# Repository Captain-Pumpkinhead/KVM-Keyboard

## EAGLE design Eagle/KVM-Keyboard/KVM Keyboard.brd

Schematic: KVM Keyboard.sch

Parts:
A: KEYSWITCH-PLAIN-CHOC-1U; CHOC-1U
B: KEYSWITCH-PLAIN-CHOC-1U; CHOC-1U
BACKSLASH: KEYSWITCH-PLAIN-CHOC-1U; CHOC-1U
BACKSPACE: KEYSWITCH-PLAIN-CHOC-2U; CHOC-2U
BLUE_ROTENC: ENCODER-SWITCH; ROTARY_ENC_PLAIN
BRACE-CLOSING: KEYSWITCH-PLAIN-CHOC-1U; CHOC-1U
BRACE-OPENING: KEYSWITCH-PLAIN-CHOC-1U; CHOC-1U
BRIGHTNESS: ENCODER-SWITCH; ROTARY_ENC_PLAIN
BRIGHTNESS-MINUS: KEYSWITCH-PLAIN-CHOC-1U; CHOC-1U
BRIGHTNESS-PLUS: KEYSWITCH-PLAIN-CHOC-1U; CHOC-1U
C: KEYSWITCH-PLAIN-CHOC-1U; CHOC-1U
CALC: KEYSWITCH-PLAIN-CHOC-1U; CHOC-1U
CAPS-LOCK: KEYSWITCH-PLAIN-CHOC-1U; CHOC-1U
COLON: KEYSWITCH-PLAIN-CHOC-1U; CHOC-1U
D: KEYSWITCH-PLAIN-CHOC-1U; CHOC-1U
D1, D2, D3, D4, D5, D6, D7, D8, D9, D10, D11, D12: DIODESMALL; DIODE_SMALL
DELETE: KEYSWITCH-PLAIN-CHOC-1U; CHOC-1U
DOWN: KEYSWITCH-PLAIN-CHOC-1U; CHOC-1U
E: KEYSWITCH-PLAIN-CHOC-1U; CHOC-1U
END: KEYSWITCH-PLAIN-CHOC-1U; CHOC-1U
ENTER: KEYSWITCH-PLAIN-CHOC-2U; CHOC-2U
ESC: KEYSWITCH-PLAIN-CHOC-1U; CHOC-1U
F, F1, F2, F3, F4, F5, F6, F7, F8, F9, F10, F11, F12: KEYSWITCH-PLAIN-CHOC-1U; CHOC-1U
FN: SWITCH_PUSHBUTTONEVQ-PE; TACT_PANA-EVQ
FOLDER: KEYSWITCH-PLAIN-CHOC-1U; CHOC-1U
G: KEYSWITCH-PLAIN-CHOC-1U; CHOC-1U
GREATER-THAN: KEYSWITCH-PLAIN-CHOC-1U; CHOC-1U
GREEN_ROTENC: ENCODER-SWITCH; ROTARY_ENC_PLAIN
H: KEYSWITCH-PLAIN-CHOC-1U; CHOC-1U
HIBERNATE: KEYSWITCH-PLAIN-CHOC-1U; CHOC-1U
HOME: KEYSWITCH-PLAIN-CHOC-1U; CHOC-1U
I: KEYSWITCH-PLAIN-CHOC-1U; CHOC-1U
INSERT: KEYSWITCH-PLAIN-CHOC-1U; CHOC-1U
J: KEYSWITCH-PLAIN-CHOC-1U; CHOC-1U
K: KEYSWITCH-PLAIN-CHOC-1U; CHOC-1U
KVM_PC1, KVM_PC2, KVM_PC3, KVM_PC4: KEYSWITCH-PLAIN-CHOC-1U; CHOC-1U
L: KEYSWITCH-PLAIN-CHOC-1U; CHOC-1U
LCD-BUTTON-BOTTOM: SWITCH_PUSHBUTTONEVQ-PE; TACT_PANA-EVQ
LCD-BUTTON-TOP: SWITCH_PUSHBUTTONEVQ-PE; TACT_PANA-EVQ
LEFT: KEYSWITCH-PLAIN-CHOC-1U; CHOC-1U
LEFT-ALT: KEYSWITCH-PLAIN-CHOC-1U; CHOC-1U
LEFT-CTRL: KEYSWITCH-PLAIN-CHOC-1U; CHOC-1U
LEFT-SUPER: KEYSWITCH-PLAIN-CHOC-1U; CHOC-1U
LESS-THAN: KEYSWITCH-PLAIN-CHOC-1U; CHOC-1U
LSHIFT: KEYSWITCH-PLAIN-CHOC-2U; CHOC-2U
M: KEYSWITCH-PLAIN-CHOC-1U; CHOC-1U
MENU: KEYSWITCH-PLAIN-CHOC-1U; CHOC-1U
MUTE: KEYSWITCH-PLAIN-CHOC-1U; CHOC-1U
N: KEYSWITCH-PLAIN-CHOC-1U; CHOC-1U
NEXT: KEYSWITCH-PLAIN-CHOC-1U; CHOC-1U
NOTES: KEYSWITCH-PLAIN-CHOC-1U; CHOC-1U
NUM0, NUM1, NUM2, NUM3, NUM4, NUM5, NUM6, NUM7, NUM8, NUM9: KEYSWITCH-PLAIN-CHOC-1U; CHOC-1U
NUM-LOCK: KEYSWITCH-PLAIN-CHOC-1U; CHOC-1U
NUM-MINUS: KEYSWITCH-PLAIN-CHOC-1U; CHOC-1U
NUM-PLUS: KEYSWITCH-PLAIN-CHOC-1U; CHOC-1U
O: KEYSWITCH-PLAIN-CHOC-1U; CHOC-1U
P: KEYSWITCH-PLAIN-CHOC-1U; CHOC-1U
PAD0: KEYSWITCH-PLAIN-CHOC-2U; CHOC-2U
PAD1, PAD2, PAD3, PAD4, PAD5, PAD6, PAD7, PAD8, PAD9: KEYSWITCH-PLAIN-CHOC-1U; CHOC-1U
PAD-ASTERISK: KEYSWITCH-PLAIN-CHOC-1U; CHOC-1U
PAD-ENTER: KEYSWITCH-PLAIN-CHOC-2U; CHOC-2U
PAD-MINUS: KEYSWITCH-PLAIN-CHOC-1U; CHOC-1U
PAD-PERIOD: KEYSWITCH-PLAIN-CHOC-1U; CHOC-1U
PAD-PLUS: KEYSWITCH-PLAIN-CHOC-2U; CHOC-2U
PAD-SLASH: KEYSWITCH-PLAIN-CHOC-1U; CHOC-1U
PAGE-DOWN: KEYSWITCH-PLAIN-CHOC-1U; CHOC-1U
PAGE-UP: KEYSWITCH-PLAIN-CHOC-1U; CHOC-1U
PLAY-PAUSE: KEYSWITCH-PLAIN-CHOC-1U; CHOC-1U
PRESENT: KEYSWITCH-PLAIN-CHOC-1U; CHOC-1U
PREVIOUS: KEYSWITCH-PLAIN-CHOC-1U; CHOC-1U
PRINT-SCREEN: KEYSWITCH-PLAIN-CHOC-1U; CHOC-1U
Q: KEYSWITCH-PLAIN-CHOC-1U; CHOC-1U
QUESTION-MARK: KEYSWITCH-PLAIN-CHOC-1U; CHOC-1U
QUOTATION-MARK: KEYSWITCH-PLAIN-CHOC-1U; CHOC-1U
R: KEYSWITCH-PLAIN-CHOC-1U; CHOC-1U
RECORD: KEYSWITCH-PLAIN-CHOC-1U; CHOC-1U
RED_ROTENC: ENCODER-SWITCH; ROTARY_ENC_PLAIN
RES-ABOVE-F10: KEYSWITCH-PLAIN-CHOC-1U; CHOC-1U
RES-BY-ESC: KEYSWITCH-PLAIN-CHOC-1U; CHOC-1U
RES-DELETE: SWITCH_PUSHBUTTONEVQ-PE; TACT_PANA-EVQ
RES-END: SWITCH_PUSHBUTTONEVQ-PE; TACT_PANA-EVQ
RES-LEFT: SWITCH_PUSHBUTTONEVQ-PE; TACT_PANA-EVQ
RES-PGDN: SWITCH_PUSHBUTTONEVQ-PE; TACT_PANA-EVQ
RES-RIGHT: SWITCH_PUSHBUTTONEVQ-PE; TACT_PANA-EVQ
RGB_A: LED-RGBNO_IC; LED-TRICOLOR-5050
RGB_B: LED-RGBNO_IC; LED-TRICOLOR-5050
RGB_BACKSLASH: LED-RGBNO_IC; LED-TRICOLOR-5050
RGB_BACKSPACE: LED-RGBNO_IC; LED-TRICOLOR-5050
RGB_BLUE-ROTENC: LED-RGBNO_IC; LED-TRICOLOR-5050
RGB_BRACE-CLOSING: LED-RGBNO_IC; LED-TRICOLOR-5050
RGB_BRACE-OPENING: LED-RGBNO_IC; LED-TRICOLOR-5050
RGB_BRIGHTNESS: LED-RGBNO_IC; LED-TRICOLOR-5050
RGB_BRIGHTNESS-MINUS: LED-RGBNO_IC; LED-TRICOLOR-5050
RGB_BRIGHTNESS-PLUS: LED-RGBNO_IC; LED-TRICOLOR-5050
RGB_C: LED-RGBNO_IC; LED-TRICOLOR-5050
RGB_CALC: LED-RGBNO_IC; LED-TRICOLOR-5050
RGB_CAPS-LOCK: LED-RGBNO_IC; LED-TRICOLOR-5050
RGB_COLON: LED-RGBNO_IC; LED-TRICOLOR-5050
RGB_D: LED-RGBNO_IC; LED-TRICOLOR-5050
RGB_DELETE: LED-RGBNO_IC; LED-TRICOLOR-5050
RGB_DOWN: LED-RGBNO_IC; LED-TRICOLOR-5050
RGB_E: LED-RGBNO_IC; LED-TRICOLOR-5050
RGB_END: LED-RGBNO_IC; LED-TRICOLOR-5050
RGB_ENTER: LED-RGBNO_IC; LED-TRICOLOR-5050
RGB_ESC: LED-RGBNO_IC; LED-TRICOLOR-5050
RGB_F, RGB_F1, RGB_F2, RGB_F3, RGB_F4, RGB_F5, RGB_F6, RGB_F7, RGB_F8, RGB_F9, RGB_F10, RGB_F11, RGB_F12: LED-RGBNO_IC; LED-TRICOLOR-5050
RGB_FN: LED-RGBNO_IC; LED-TRICOLOR-5050
RGB_FOLDER: LED-RGBNO_IC; LED-TRICOLOR-5050
RGB_G: LED-RGBNO_IC; LED-TRICOLOR-5050
RGB_GREATER-THAN: LED-RGBNO_IC; LED-TRICOLOR-5050
RGB_GREEN-ROTENC: LED-RGBNO_IC; LED-TRICOLOR-5050
RGB_H: LED-RGBNO_IC; LED-TRICOLOR-5050
RGB_HIBERNATE: LED-RGBNO_IC; LED-TRICOLOR-5050
RGB_HOME: LED-RGBNO_IC; LED-TRICOLOR-5050
RGB_I: LED-RGBNO_IC; LED-TRICOLOR-5050
RGB_INSERT: LED-RGBNO_IC; LED-TRICOLOR-5050
RGB_J: LED-RGBNO_IC; LED-TRICOLOR-5050
RGB_K: LED-RGBNO_IC; LED-TRICOLOR-5050
RGB_KVM-PC1, RGB_KVM-PC2, RGB_KVM-PC3, RGB_KVM-PC4: LED-RGBNO_IC; LED-TRICOLOR-5050
RGB_L: LED-RGBNO_IC; LED-TRICOLOR-5050
RGB_LCD-BUTTON-BOTTOM: LED-RGBNO_IC; LED-TRICOLOR-5050
RGB_LCD-BUTTON-TOP: LED-RGBNO_IC; LED-TRICOLOR-5050
RGB_LEFT: LED-RGBNO_IC; LED-TRICOLOR-5050
RGB_LEFT-ALT: LED-RGBNO_IC; LED-TRICOLOR-5050
RGB_LEFT-CTRL: LED-RGBNO_IC; LED-TRICOLOR-5050
RGB_LEFT-SUPER: LED-RGBNO_IC; LED-TRICOLOR-5050
RGB_LESS-THAN: LED-RGBNO_IC; LED-TRICOLOR-5050
RGB_LSHIFT: LED-RGBNO_IC; LED-TRICOLOR-5050
RGB_M: LED-RGBNO_IC; LED-TRICOLOR-5050
RGB_MENU: LED-RGBNO_IC; LED-TRICOLOR-5050
RGB_MUTE: LED-RGBNO_IC; LED-TRICOLOR-5050
RGB_N: LED-RGBNO_IC; LED-TRICOLOR-5050
RGB_NEXT: LED-RGBNO_IC; LED-TRICOLOR-5050
RGB_NOTES: LED-RGBNO_IC; LED-TRICOLOR-5050
RGB_NUM0, RGB_NUM1, RGB_NUM2, RGB_NUM3, RGB_NUM4, RGB_NUM5, RGB_NUM6, RGB_NUM7, RGB_NUM8, RGB_NUM9: LED-RGBNO_IC; LED-TRICOLOR-5050
RGB_NUM-LOCK: LED-RGBNO_IC; LED-TRICOLOR-5050
RGB_NUM-MINUS: LED-RGBNO_IC; LED-TRICOLOR-5050
RGB_NUM-PLUS: LED-RGBNO_IC; LED-TRICOLOR-5050
RGB_O: LED-RGBNO_IC; LED-TRICOLOR-5050
RGB_P: LED-RGBNO_IC; LED-TRICOLOR-5050
RGB_PAD0, RGB_PAD1, RGB_PAD2, RGB_PAD3, RGB_PAD4, RGB_PAD5, RGB_PAD6, RGB_PAD7, RGB_PAD8, RGB_PAD9: LED-RGBNO_IC; LED-TRICOLOR-5050
RGB_PAD-ASTERISK: LED-RGBNO_IC; LED-TRICOLOR-5050
RGB_PAD-ENTER: LED-RGBNO_IC; LED-TRICOLOR-5050
RGB_PAD-MINUS: LED-RGBNO_IC; LED-TRICOLOR-5050
RGB_PAD-PERIOD: LED-RGBNO_IC; LED-TRICOLOR-5050
RGB_PAD-PLUS: LED-RGBNO_IC; LED-TRICOLOR-5050
RGB_PAD-SLASH: LED-RGBNO_IC; LED-TRICOLOR-5050
RGB_PAGE-DOWN: LED-RGBNO_IC; LED-TRICOLOR-5050
RGB_PAGE-UP: LED-RGBNO_IC; LED-TRICOLOR-5050
RGB_PLAY-PAUSE: LED-RGBNO_IC; LED-TRICOLOR-5050
RGB_PRESENT: LED-RGBNO_IC; LED-TRICOLOR-5050
RGB_PREVIOUS: LED-RGBNO_IC; LED-TRICOLOR-5050
RGB_PRINT-SCREEN: LED-RGBNO_IC; LED-TRICOLOR-5050
RGB_Q: LED-RGBNO_IC; LED-TRICOLOR-5050
RGB_QUESTION-MARK: LED-RGBNO_IC; LED-TRICOLOR-5050
RGB_QUOTATION-MARK: LED-RGBNO_IC; LED-TRICOLOR-5050
RGB_R: LED-RGBNO_IC; LED-TRICOLOR-5050
RGB_RECORD: LED-RGBNO_IC; LED-TRICOLOR-5050
RGB_RED-ROTENC: LED-RGBNO_IC; LED-TRICOLOR-5050
RGB_RES-ABOVE-F10: LED-RGBNO_IC; LED-TRICOLOR-5050
RGB_RES-BY-ESC: LED-RGBNO_IC; LED-TRICOLOR-5050
RGB_RES-DELETE: LED-RGBNO_IC; LED-TRICOLOR-5050
RGB_RES-END: LED-RGBNO_IC; LED-TRICOLOR-5050
RGB_RES-LEFT: LED-RGBNO_IC; LED-TRICOLOR-5050
RGB_RES-PGDN: LED-RGBNO_IC; LED-TRICOLOR-5050
RGB_RES-RIGHT: LED-RGBNO_IC; LED-TRICOLOR-5050
RGB_RIGHT: LED-RGBNO_IC; LED-TRICOLOR-5050
RGB_RIGHT-ALT: LED-RGBNO_IC; LED-TRICOLOR-5050
RGB_RIGHT-CTRL: LED-RGBNO_IC; LED-TRICOLOR-5050
RGB_RIGHT-SUPER: LED-RGBNO_IC; LED-TRICOLOR-5050
RGB_RSHIFT: LED-RGBNO_IC; LED-TRICOLOR-5050
RGB_S: LED-RGBNO_IC; LED-TRICOLOR-5050
RGB_SAVE-CLIP: LED-RGBNO_IC; LED-TRICOLOR-5050
RGB_SKIP-BACK: LED-RGBNO_IC; LED-TRICOLOR-5050
RGB_SKIP-FORWARD: LED-RGBNO_IC; LED-TRICOLOR-5050
RGB_SLEEP: LED-RGBNO_IC; LED-TRICOLOR-5050
RGB_SPACE: LED-RGBNO_IC; LED-TRICOLOR-5050
RGB_STOP: LED-RGBNO_IC; LED-TRICOLOR-5050
RGB_T: LED-RGBNO_IC; LED-TRICOLOR-5050
RGB_TAB: LED-RGBNO_IC; LED-TRICOLOR-5050
RGB_TILDA: LED-RGBNO_IC; LED-TRICOLOR-5050
RGB_U: LED-RGBNO_IC; LED-TRICOLOR-5050
RGB_UP: LED-RGBNO_IC; LED-TRICOLOR-5050
RGB_V: LED-RGBNO_IC; LED-TRICOLOR-5050
RGB_VOLUME-MASTER: LED-RGBNO_IC; LED-TRICOLOR-5050
RGB_VOLUME-PC1, RGB_VOLUME-PC2, RGB_VOLUME-PC3, RGB_VOLUME-PC4: LED-RGBNO_IC; LED-TRICOLOR-5050
RGB_W: LED-RGBNO_IC; LED-TRICOLOR-5050
RGB_X: LED-RGBNO_IC; LED-TRICOLOR-5050
RGB_Y: LED-RGBNO_IC; LED-TRICOLOR-5050
RGB_Z: LED-RGBNO_IC; LED-TRICOLOR-5050
RIGHT: KEYSWITCH-PLAIN-CHOC-1U; CHOC-1U
RIGHT-ALT: KEYSWITCH-PLAIN-CHOC-1U; CHOC-1U
RIGHT-CTRL: KEYSWITCH-PLAIN-CHOC-1U; CHOC-1U
RIGHT-SUPER: KEYSWITCH-PLAIN-CHOC-1U; CHOC-1U
RSHIFT: KEYSWITCH-PLAIN-CHOC-2U; CHOC-2U
S: KEYSWITCH-PLAIN-CHOC-1U; CHOC-1U
SAVE_CLIP: KEYSWITCH-PLAIN-CHOC-1U; CHOC-1U
SKIP-BACK: KEYSWITCH-PLAIN-CHOC-1U; CHOC-1U
SKIP-FORWARD: KEYSWITCH-PLAIN-CHOC-1U; CHOC-1U
SLEEP: KEYSWITCH-PLAIN-CHOC-1U; CHOC-1U
SPACE: KEYSWITCH-PLAIN-CHOC-6.25U; CHOC-6.25U
STOP: KEYSWITCH-PLAIN-CHOC-1U; CHOC-1U
T: KEYSWITCH-PLAIN-CHOC-1U; CHOC-1U
TAB: KEYSWITCH-PLAIN-CHOC-1U; CHOC-1U
TILDA: KEYSWITCH-PLAIN-CHOC-1U; CHOC-1U
U: KEYSWITCH-PLAIN-CHOC-1U; CHOC-1U
U1, U2, U3, U4, U5: RP2040; IC57_RP2040
U6, U7: MUX.DEMUX-8X.2:2_PI3PCIE3242AZLEX; 30-WFQFN_EXPOSED.PAD
U$1: USB.HUB-USB3.1-6.PORT__USB7206C/KDXVQFN100_KDX_MCH; VQFN100_KDX_MCH
U$2, U$3, U$4, U$5, U$6: QSPI-FLASH__W25Q128JVSIM-ND; SO08
UP: KEYSWITCH-PLAIN-CHOC-1U; CHOC-1U
USB1, USB2, USB3, USB4, USB5, USB6: USB-C_RECEPTACLE
V: KEYSWITCH-PLAIN-CHOC-1U; CHOC-1U
VOLUME_MASTER: ENCODER-SWITCH; ROTARY_ENC_PLAIN
VOLUME_PC1, VOLUME_PC2, VOLUME_PC3, VOLUME_PC4: ENCODER-SWITCH; ROTARY_ENC_PLAIN
W: KEYSWITCH-PLAIN-CHOC-1U; CHOC-1U
X: KEYSWITCH-PLAIN-CHOC-1U; CHOC-1U
Y: KEYSWITCH-PLAIN-CHOC-1U; CHOC-1U
Z: KEYSWITCH-PLAIN-CHOC-1U; CHOC-1U

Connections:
9.VCORE: U$1.9 (9.VCORE)
13.GND: U6.13 (13.GND), U7.13 (13.GND)
18.VCORE: U$1.18 (18.VCORE)
25.VCORE: U$1.25 (25.VCORE)
26.VDD33: U$1.26 (26.VDD33)
31.VCORE: U$1.31 (31.VCORE)
38.VCORE: U$1.38 (38.VCORE)
43.VDD33: U$1.43 (43.VDD33)
53.VDD33: U$1.53 (53.VDD33)
55.VCORE: U$1.55 (55.VCORE)
62.VDD33: U$1.62 (62.VDD33)
67.VDD33: U$1.67 (67.VDD33)
78.VCORE: U$1.78 (78.VCORE)
79.VDD33: U$1.79 (79.VDD33)
85.VCORE: U$1.85 (85.VCORE)
88.VDD33: U$1.88 (88.VDD33)
93.VCORE: U$1.93 (93.VCORE)
99.VDD33: U$1.99 (99.VDD33)
ADC_AVDD: U1.43 (ADC_AVDD), U2.43 (ADC_AVDD), U3.43 (ADC_AVDD), U4.43 (ADC_AVDD), U5.43 (ADC_AVDD)
DVDD: U1.50 (DVDD), U2.50 (DVDD), U3.50 (DVDD), U4.50 (DVDD), U5.50 (DVDD)
DVDD_2: U1.23 (DVDD_2), U2.23 (DVDD_2), U3.23 (DVDD_2), U4.23 (DVDD_2), U5.23 (DVDD_2)
GND: D1.A, D3.A, D6.A, D7.A, D10.A, D11.A, U$1.101 (101.VSS)
IOVDD: U1.49 (IOVDD), U2.49 (IOVDD), U3.49 (IOVDD), U4.49 (IOVDD), U5.49 (IOVDD)
IOVDD_2: U1.1 (IOVDD_2), U2.1 (IOVDD_2), U3.1 (IOVDD_2), U4.1 (IOVDD_2), U5.1 (IOVDD_2)
IOVDD_3: U1.10 (IOVDD_3), U2.10 (IOVDD_3), U3.10 (IOVDD_3), U4.10 (IOVDD_3), U5.10 (IOVDD_3)
IOVDD_4: U1.22 (IOVDD_4), U2.22 (IOVDD_4), U3.22 (IOVDD_4), U4.22 (IOVDD_4), U5.22 (IOVDD_4)
IOVDD_5: U1.33 (IOVDD_5), U2.33 (IOVDD_5), U3.33 (IOVDD_5), U4.33 (IOVDD_5), U5.33 (IOVDD_5)
IOVDD_6: U1.42 (IOVDD_6), U2.42 (IOVDD_6), U3.42 (IOVDD_6), U4.42 (IOVDD_6), U5.42 (IOVDD_6)
unnamed: U1.56 (QSPI_SS_N), U$2.1 (/CS)
unnamed: U1.52 (QSPI_SCLK), U$2.6 (CLK)
unnamed: U1.53 (QSPI_SD0), U$2.5 (IO0(DI))
unnamed: U1.55 (QSPI_SD1), U$2.2 (IO1(DO))
unnamed: U1.54 (QSPI_SD2), U$2.3 (IO2(/WP))
unnamed: U1.51 (QSPI_SD3), U$2.7 (IO3)
unnamed: U2.56 (QSPI_SS_N), U$3.1 (/CS)
unnamed: U2.51 (QSPI_SD3), U$3.7 (IO3)
unnamed: U2.52 (QSPI_SCLK), U$3.6 (CLK)
unnamed: U2.53 (QSPI_SD0), U$3.5 (IO0(DI))
unnamed: U2.54 (QSPI_SD2), U$3.3 (IO2(/WP))
unnamed: U2.55 (QSPI_SD1), U$3.2 (IO1(DO))
unnamed: U3.56 (QSPI_SS_N), U$4.1 (/CS)
unnamed: U3.51 (QSPI_SD3), U$4.7 (IO3)
unnamed: U3.52 (QSPI_SCLK), U$4.6 (CLK)
unnamed: U3.53 (QSPI_SD0), U$4.5 (IO0(DI))
unnamed: U3.54 (QSPI_SD2), U$4.3 (IO2(/WP))
unnamed: U3.55 (QSPI_SD1), U$4.2 (IO1(DO))
unnamed: U4.56 (QSPI_SS_N), U$5.1 (/CS)
unnamed: U4.51 (QSPI_SD3), U$5.7 (IO3)
unnamed: U4.52 (QSPI_SCLK), U$5.6 (CLK)
unnamed: U4.53 (QSPI_SD0), U$5.5 (IO0(DI))
unnamed: U4.54 (QSPI_SD2), U$5.3 (IO2(/WP))
unnamed: U4.55 (QSPI_SD1), U$5.2 (IO1(DO))
unnamed: U5.56 (QSPI_SS_N), U$6.1 (/CS)
unnamed: U5.51 (QSPI_SD3), U$6.7 (IO3)
unnamed: U5.52 (QSPI_SCLK), U$6.6 (CLK)
unnamed: U5.53 (QSPI_SD0), U$6.5 (IO0(DI))
unnamed: U5.54 (QSPI_SD2), U$6.3 (IO2(/WP))
unnamed: U5.55 (QSPI_SD1), U$6.2 (IO1(DO))
OE#: U6.29 (OE#), U7.29 (OE#)
PICO.D+: U5.47 (USB_DP)
PICO.D-: U5.46 (USB_DM)
SEL: U6.5 (SEL), U7.5 (SEL)
USB1.CC1: USB1.A5
USB1.CC2: USB1.B5
USB1.D+: USB1.A6, USB1.B6
USB1.D-: USB1.A7, USB1.B7
USB1.GND: D1.C, USB1.A1, USB1.A12, USB1.B1, USB1.B12
USB1.R+: USB1.B11
USB1.RX+: USB1.A11
USB1.RX-: USB1.A10
USB1.SBU: USB1.A8, USB1.B8, USB1.B9
USB1.TX+: USB1.A2, USB1.B2
USB1.TX-: USB1.A3, USB1.B3
USB1.VBUS: D2.A, USB1.A4, USB1.A9, USB1.B4
USB1RX-: USB1.B10
USB2.CC1: USB2.A5
USB2.CC2: USB2.B5
USB2.D+: USB2.A6, USB2.B6
USB2.D-: USB2.A7, USB2.B7
USB2.GND: D3.C, USB2.A1, USB2.A12, USB2.B1, USB2.B12
USB2.RX+: USB2.A11, USB2.B11
USB2.RX-: USB2.A10, USB2.B10
USB2.SBU: USB2.A8, USB2.B8
USB2.TX+: USB2.A2, USB2.B2
USB2.TX-: USB2.A3, USB2.B3
USB2.VBUS: D4.A, USB2.A4, USB2.A9, USB2.B4, USB2.B9
USB3.CC1: USB3.A5
USB3.CC2: USB3.B5
USB3.D+: USB3.A6, USB3.B6
USB3.D-: USB3.A7, USB3.B7
USB3.GND: D6.C, USB3.A1, USB3.A12, USB3.B1, USB3.B12
USB3.RX+: USB3.A11, USB3.B11
USB3.RX-: USB3.A10, USB3.B10
USB3.SBU: USB3.A8, USB3.B8
USB3.TX+: USB3.A2, USB3.B2
USB3.TX-: USB3.A3, USB3.B3
USB3.VBUS: D5.A, USB3.A4, USB3.A9, USB3.B4, USB3.B9
USB4.CC1: USB4.A5
USB4.CC2: USB4.B5
USB4.D+: USB4.A6, USB4.B6
USB4.D-: USB4.A7, USB4.B7
USB4.GND: D7.C, USB4.A1, USB4.A12, USB4.B1, USB4.B12
USB4.RX+: USB4.A11, USB4.B11
USB4.RX-: USB4.A10, USB4.B10
USB4.SBU: USB4.A8, USB4.B8
USB4.TX+: USB4.A2, USB4.B2
USB4.TX-: USB4.A3, USB4.B3
USB4.VBUS: D8.A, USB4.A4, USB4.A9, USB4.B4, USB4.B9
USB5.CC1: USB5.A5
USB5.CC2: USB5.B5
USB5.D+: USB5.A6, USB5.B6
USB5.D-: USB5.A7, USB5.B7
USB5.GND: D10.C, USB5.A1, USB5.A12, USB5.B1, USB5.B12
USB5.RX+: USB5.A11, USB5.B11
USB5.RX-: USB5.A10, USB5.B10
USB5.SBU: USB5.A8, USB5.B8
USB5.TX+: USB5.A2, USB5.B2
USB5.TX-: USB5.A3, USB5.B3
USB5.VBUS: D9.A, USB5.A4, USB5.A9, USB5.B4, USB5.B9
USB6.CC1: USB6.A5
USB6.CC2: USB6.B5
USB6.D+: USB6.A6, USB6.B6
USB6.D-: USB6.A7, USB6.B7
USB6.GND: D11.C, USB6.A1, USB6.A12, USB6.B1, USB6.B12
USB6.RX+: USB6.A11, USB6.B11
USB6.RX-: USB6.A10, USB6.B10
USB6.SBU: USB6.A8, USB6.B8
USB6.TX+: USB6.A2, USB6.B2
USB6.TX-: USB6.A3, USB6.B3
USB6.VBUS: D12.A, USB6.A4, USB6.A9, USB6.B4, USB6.B9
USB.SHIELDING: USB1.25 (SHIELDING), USB1.26 (SHIELDING), USB1.27 (SHIELDING), USB1.28 (SHIELDING), USB2.25 (SHIELDING), USB2.26 (SHIELDING), USB2.27 (SHIELDING), USB2.28 (SHIELDING), USB3.25 (SHIELDING), USB3.26 (SHIELDING), USB3.27 (SHIELDING), USB3.28 (SHIELDING), USB4.25 (SHIELDING), USB4.26 (SHIELDING), USB4.27 (SHIELDING), USB4.28 (SHIELDING), USB5.25 (SHIELDING), USB5.26 (SHIELDING), USB5.27 (SHIELDING), USB5.28 (SHIELDING), USB6.25 (SHIELDING), USB6.26 (SHIELDING), USB6.27 (SHIELDING), USB6.28 (SHIELDING)
USB_VDD: U1.48 (USB_VDD), U2.48 (USB_VDD), U3.48 (USB_VDD), U4.48 (USB_VDD), U5.48 (USB_VDD)
VCC: D2.C, D4.C, D5.C, D8.C, D9.C, D12.C

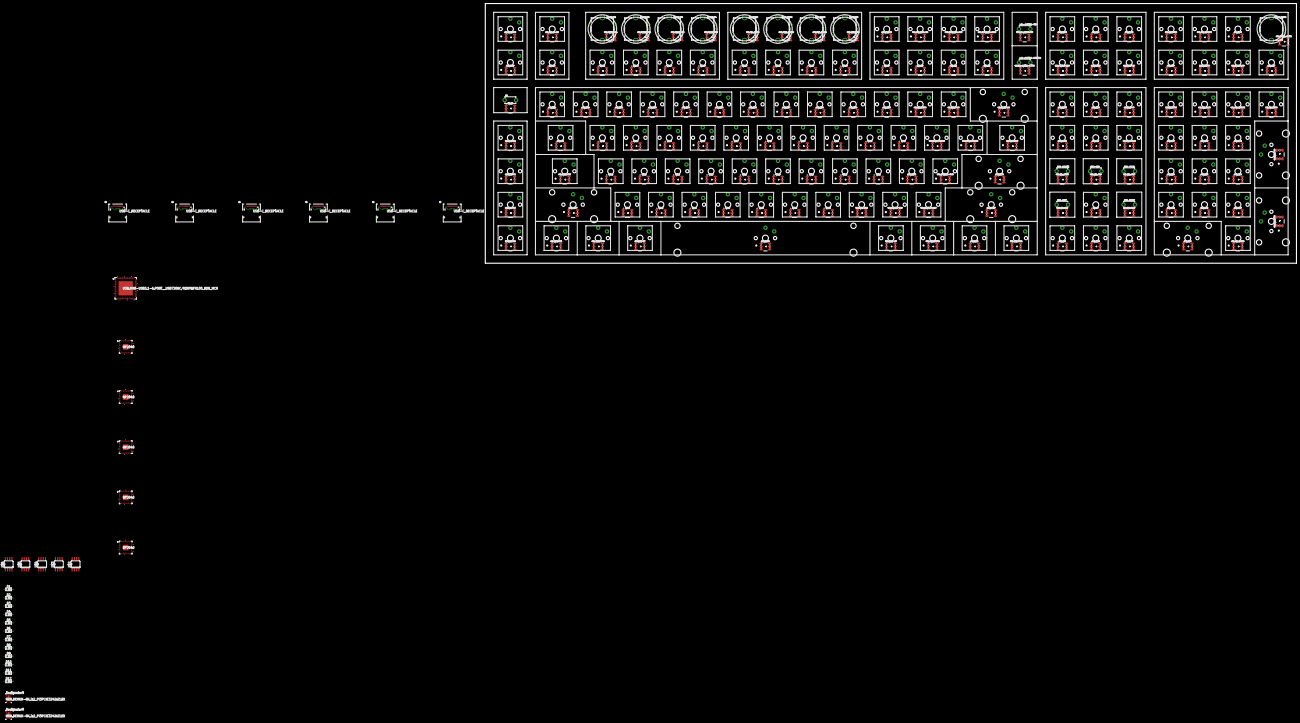
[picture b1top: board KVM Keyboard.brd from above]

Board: 2 copper layers, 460.8 x 147.5 mm, 315 parts (0 on the bottom side), 98 nets, no tracks yet.

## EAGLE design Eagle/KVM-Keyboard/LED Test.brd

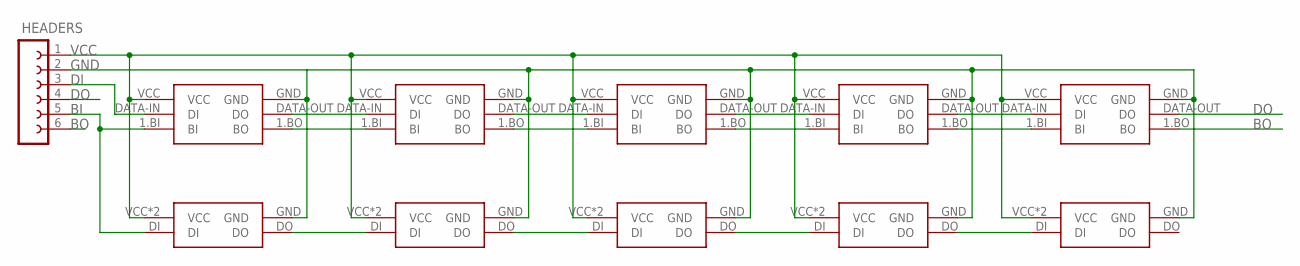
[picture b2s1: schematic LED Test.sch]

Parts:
HEADERS: FE06-1; FE06
U$1, U$2, U$3, U$4, U$5: OPTO-PIXEL.COMBINEDCOMBINED-V1.04; COMBINED4
U$6, U$7, U$8, U$9, U$10: OPTO-PIXEL.IN-PI55TBTPRPGPBIN-PI55TBTPRPGPB; IN-PI55TBTPRPGPB

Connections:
BI: HEADERS.5, U$1.1.BI (BI), U$6.DI
BO: HEADERS.6, U$5.1.BO (BO)
DI: HEADERS.3, U$1.DATA-IN (DI)
DO: HEADERS.4, U$5.DATA-OUT (DO)
GND: HEADERS.2, U$1.GND, U$2.GND, U$3.GND, U$4.GND, U$5.GND, U$6.GND, U$7.GND, U$8.GND, U$9.GND, U$10.GND
unnamed: U$1.DATA-OUT (DO), U$2.DATA-IN (DI)
unnamed: U$1.1.BO (BO), U$2.1.BI (BI)
unnamed: U$2.DATA-OUT (DO), U$3.DATA-IN (DI)
unnamed: U$2.1.BO (BO), U$3.1.BI (BI)
unnamed: U$3.1.BO (BO), U$4.1.BI (BI)
unnamed: U$3.DATA-OUT (DO), U$4.DATA-IN (DI)
unnamed: U$4.DATA-OUT (DO), U$5.DATA-IN (DI)
unnamed: U$4.1.BO (BO), U$5.1.BI (BI)
unnamed: U$6.DO, U$7.DI
unnamed: U$7.DO, U$8.DI
unnamed: U$8.DO, U$9.DI
unnamed: U$9.DO, U$10.DI
VCC: HEADERS.1, U$1.VCC, U$2.VCC, U$3.VCC, U$4.VCC, U$5.VCC, U$6.VCC, U$6.VDD (VCC), U$7.VCC, U$7.VDD (VCC), U$8.VCC, U$8.VDD (VCC), U$9.VCC, U$9.VDD (VCC), U$10.VCC, U$10.VDD (VCC)

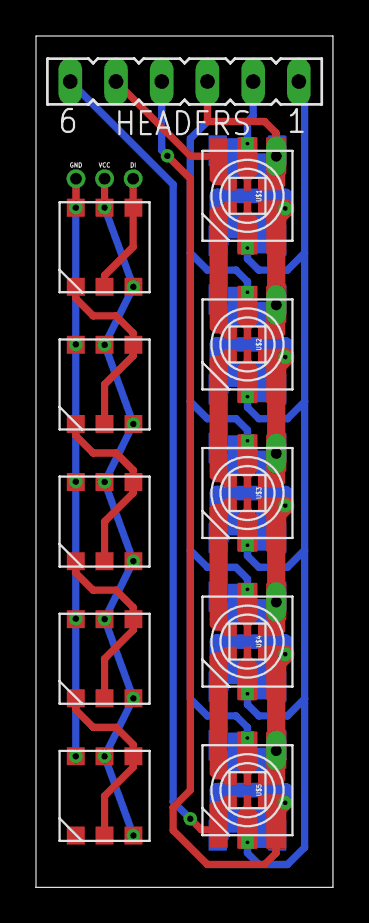
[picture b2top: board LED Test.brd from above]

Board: 2 copper layers, 16.5 x 47.3 mm, 11 parts (0 on the bottom side), 18 nets.

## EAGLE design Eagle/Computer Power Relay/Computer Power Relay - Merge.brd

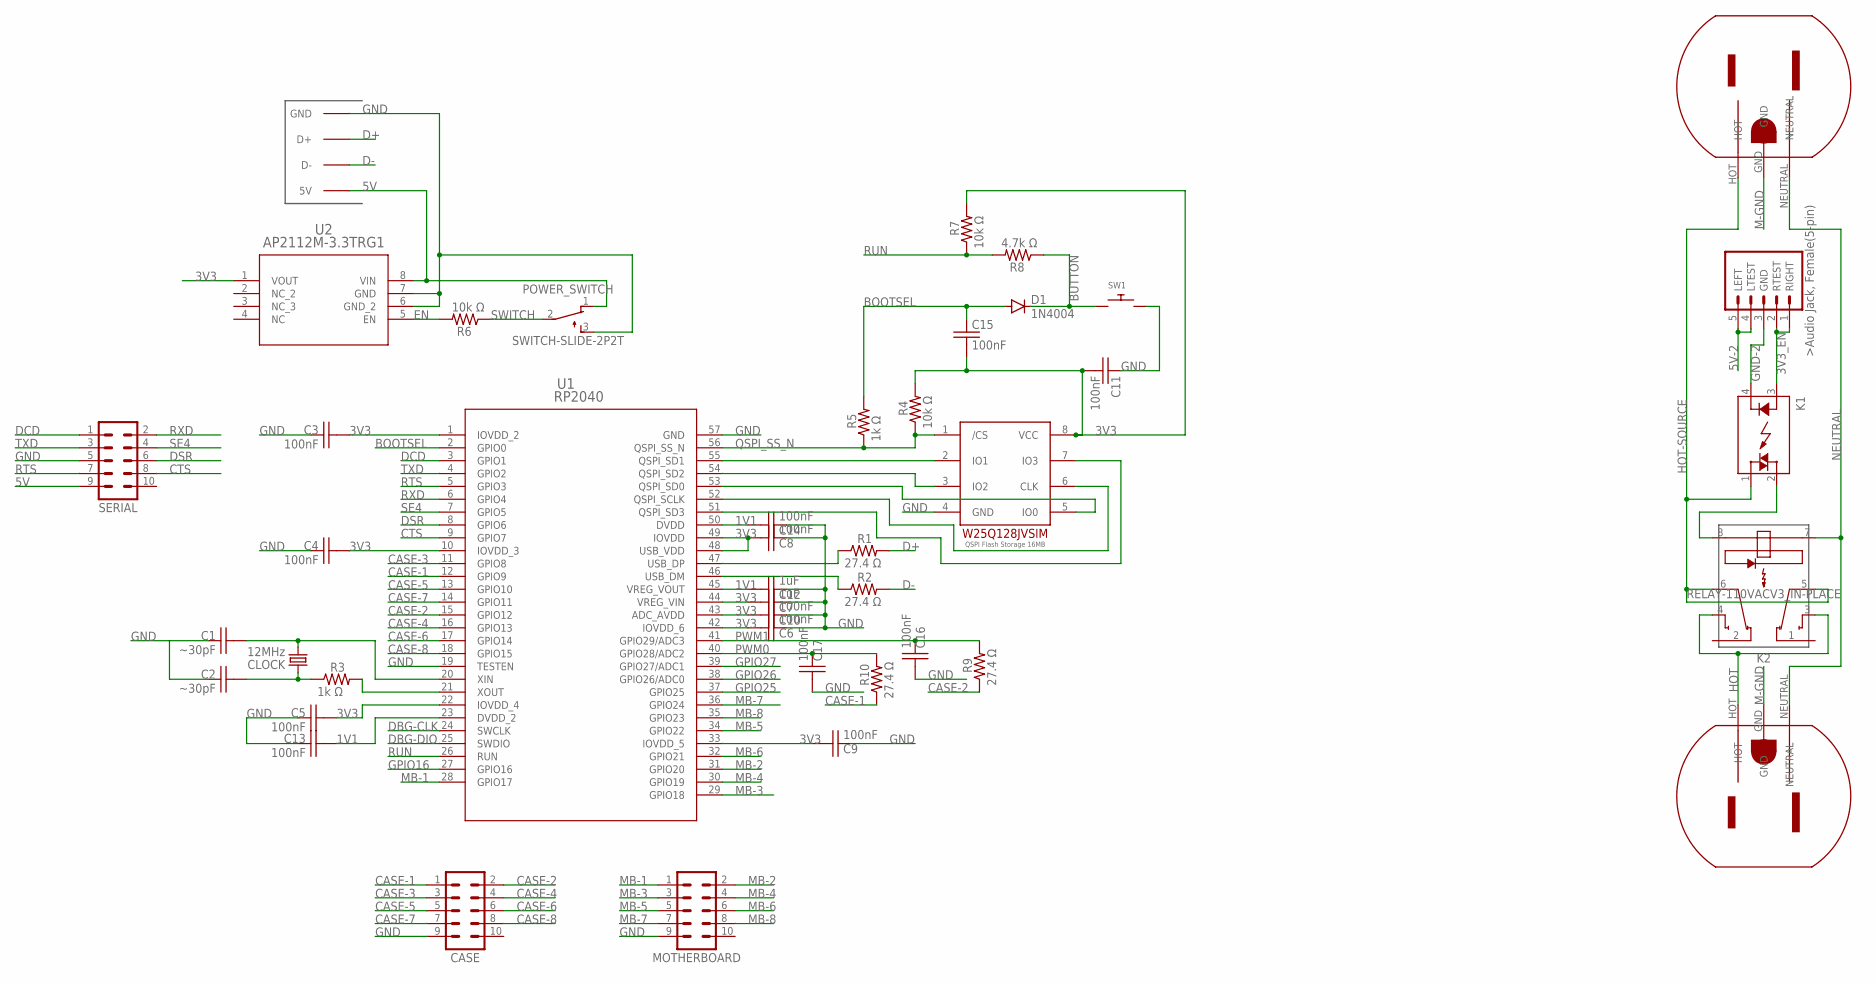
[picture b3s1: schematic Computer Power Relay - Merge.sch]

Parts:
C1, C2: ~30pF; C0402K
C3, C4, C5, C6, C8, C9, C10, C11, C13, C14, C15, C16, C17: 100nF; C0402K
C7, C12: 1uF; C0402K
CASE: MA05-2
CLOCK: 12MHz; HC49/S
D1: 1N4004; DO41-10
K1: RELAY-3V3DC-110VAC012; RELAY-3V3-110V
K2: RELAY-110VACV3_IN-PLACE; RELAY-110VAC-V3
MOTHERBOARD: MA05-2
POWER_SWITCH: SWITCH-SLIDE-2P2T
R1, R2, R9, R10: 27.4 Ω; R0603
R3, R5: 1k Ω; R0603
R4, R6, R7: 10k Ω; R0603
R8: 4.7k Ω; R0603
SERIAL: MA05-2
SW1: SWITCH_PUSHBUTTONSOFTTOUCHSMD_SJ; PUSHBUTTON_TH
U1: RP2040; IC57_RP2040
U2: AP2112M-3.3TRG1; AP2112M-3.3TRG1_DIO
U$1: W25Q128JVSIM-ND__QSPI-FLASH; SO08
U$2: PCB_USB
U$3, U$4: MAINS-POWER-OUTLET3-PIN; 3-PIN-POWER
U$5: AUDIO_JACK_FEMALE_5-PIN

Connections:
1V1: C12.2, C13.2, C14.2, U1.23 (DVDD_2), U1.45 (VREG_VOUT), U1.50 (DVDD)
3V3: C3.2, C4.2, C5.2, C6.2, C7.2, C8.2, C9.2, C10.2, C11.2, C15.2, R4.2, R7.2, U1.1 (IOVDD_2), U1.10 (IOVDD_3), U1.22 (IOVDD_4), U1.33 (IOVDD_5), U1.42 (IOVDD_6), U1.43 (ADC_AVDD), U1.44 (VREG_VIN), U1.48 (USB_VDD), U1.49 (IOVDD), U2.1 (VOUT), U$1.8 (VCC)
3V3_EN: K1.3, U$5.1 (RIGHT), U$5.2 (RTEST)
5V: POWER_SWITCH.1 (O), SERIAL.9, U2.8 (VIN), U$2.5V, U$2.5V_2 (5V)
5V-2: U$5.4 (LTEST), U$5.5 (LEFT)
BOOTSEL: C15.1, D1.A, R5.2, U1.2 (GPIO0)
BUTTON: D1.C, R8.1, SW1.P$1
CASE-1: CASE.1, R10.1, U1.12 (GPIO9)
CASE-2: CASE.2, R9.1, U1.15 (GPIO12)
CASE-3: CASE.3, U1.11 (GPIO8)
CASE-4: CASE.4, U1.16 (GPIO13)
CASE-5: CASE.5, U1.13 (GPIO10)
CASE-6: CASE.6, U1.17 (GPIO14)
CASE-7: CASE.7, U1.14 (GPIO11)
CASE-8: CASE.8, U1.18 (GPIO15)
CTS: SERIAL.8, U1.9 (GPIO7)
D+: R1.2, U$2.D+, U$2.D+_2 (D+)
D-: R2.2, U$2.D-, U$2.D-_2 (D-)
DBG-CLK: U1.24 (SWCLK)
DBG-DIO: U1.25 (SWDIO)
DCD: SERIAL.1, U1.3 (GPIO1)
DSR: SERIAL.6, U1.8 (GPIO6)
EN: R6.2, U2.5 (EN)
GND: C1.1, C2.1, C3.1, C4.1, C5.1, C6.1, C7.1, C8.1, C9.1, C10.1, C11.1, C12.1, C13.1, C14.1, C16.2, C17.2, CASE.9, MOTHERBOARD.9, POWER_SWITCH.3 (S), SERIAL.5, SW1.P$2, U1.19 (TESTEN), U1.57 (GND), U2.6 (GND_2), U2.7 (GND), U$1.4 (GND), U$2.GND, U$2.GND_2 (GND)
GND-2: K1.4, U$5.3 (GND)
GPIO16: U1.27 (GPIO16)
GPIO25: U1.37 (GPIO25)
GPIO26: U1.38 (GPIO26/ADC0)
GPIO27: U1.39 (GPIO27/ADC1)
HOT: K2.3, K2.4, U$4.HOT
HOT-SOURCE: K1.1, K2.5, K2.6, U$3.HOT
M-GND: U$3.GND, U$4.GND
MB-1: MOTHERBOARD.1, U1.28 (GPIO17)
MB-2: MOTHERBOARD.2, U1.31 (GPIO20)
MB-3: MOTHERBOARD.3, U1.29 (GPIO18)
MB-4: MOTHERBOARD.4, U1.30 (GPIO19)
MB-5: MOTHERBOARD.5, U1.34 (GPIO22)
MB-6: MOTHERBOARD.6, U1.32 (GPIO21)
MB-7: MOTHERBOARD.7, U1.36 (GPIO24)
MB-8: MOTHERBOARD.8, U1.35 (GPIO23)
unnamed: R1.1, U1.47 (USB_DP)
unnamed: R2.1, U1.46 (USB_DM)
unnamed: C2.2, CLOCK.2, R3.1
unnamed: R3.2, U1.21 (XOUT)
unnamed: C1.2, CLOCK.1, U1.20 (XIN)
unnamed: K1.2, K2.8
unnamed: U1.54 (QSPI_SD2), U$1.3 (IO2)
unnamed: U1.55 (QSPI_SD1), U$1.2 (IO1)
unnamed: U1.53 (QSPI_SD0), U$1.5 (IO0)
unnamed: U1.52 (QSPI_SCLK), U$1.6 (CLK)
unnamed: U1.51 (QSPI_SD3), U$1.7 (IO3)
NEUTRAL: K2.7, U$3.NEUTRAL, U$4.NEUTRAL
PWM0: C17.1, R10.2, U1.40 (GPIO28/ADC2)
PWM1: C16.1, R9.2, U1.41 (GPIO29/ADC3)
QSPI_SS_N: R4.1, R5.1, U1.56 (QSPI_SS_N), U$1.1 (/CS)
RTS: SERIAL.7, U1.5 (GPIO3)
RUN: R7.1, R8.2, U1.26 (RUN)
RXD: SERIAL.2, U1.6 (GPIO4)
SE4: SERIAL.4, U1.7 (GPIO5)
SWITCH: POWER_SWITCH.2, R6.1
TXD: SERIAL.3, U1.4 (GPIO2)

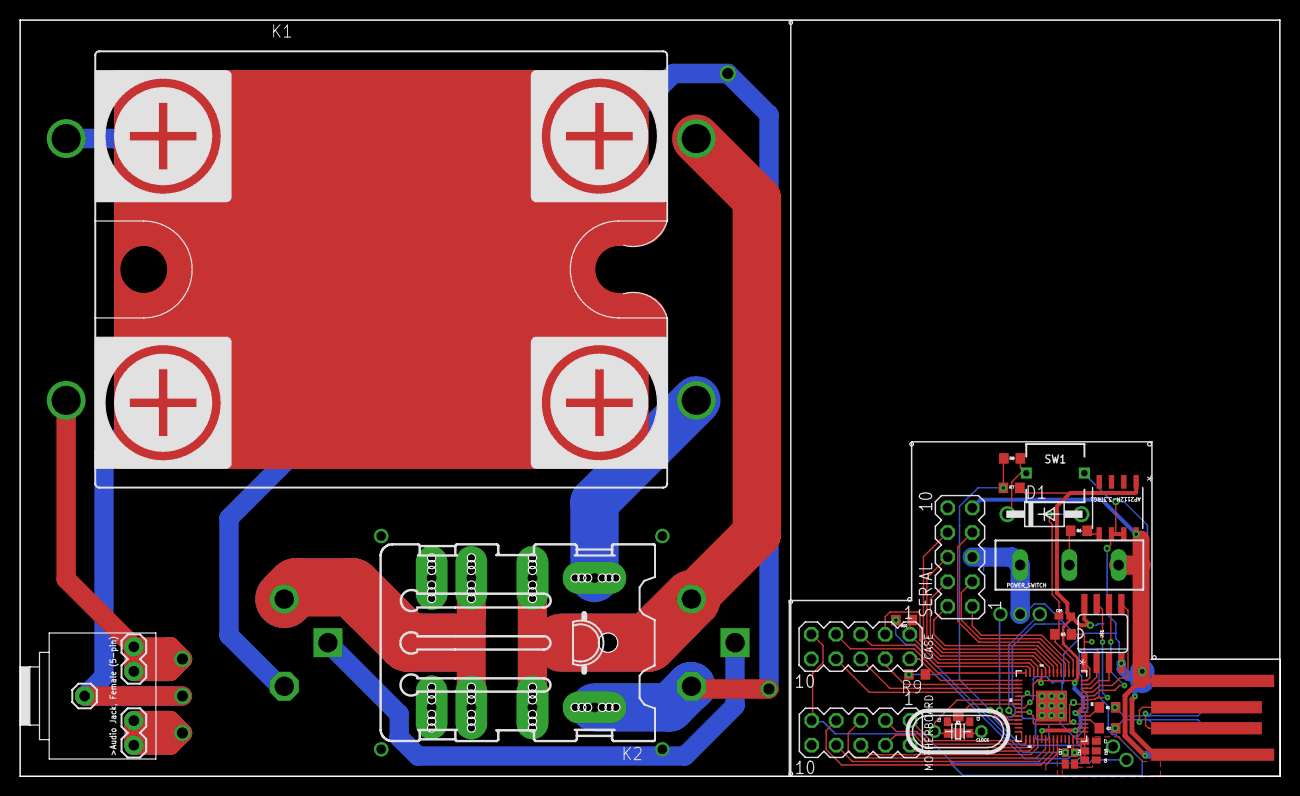
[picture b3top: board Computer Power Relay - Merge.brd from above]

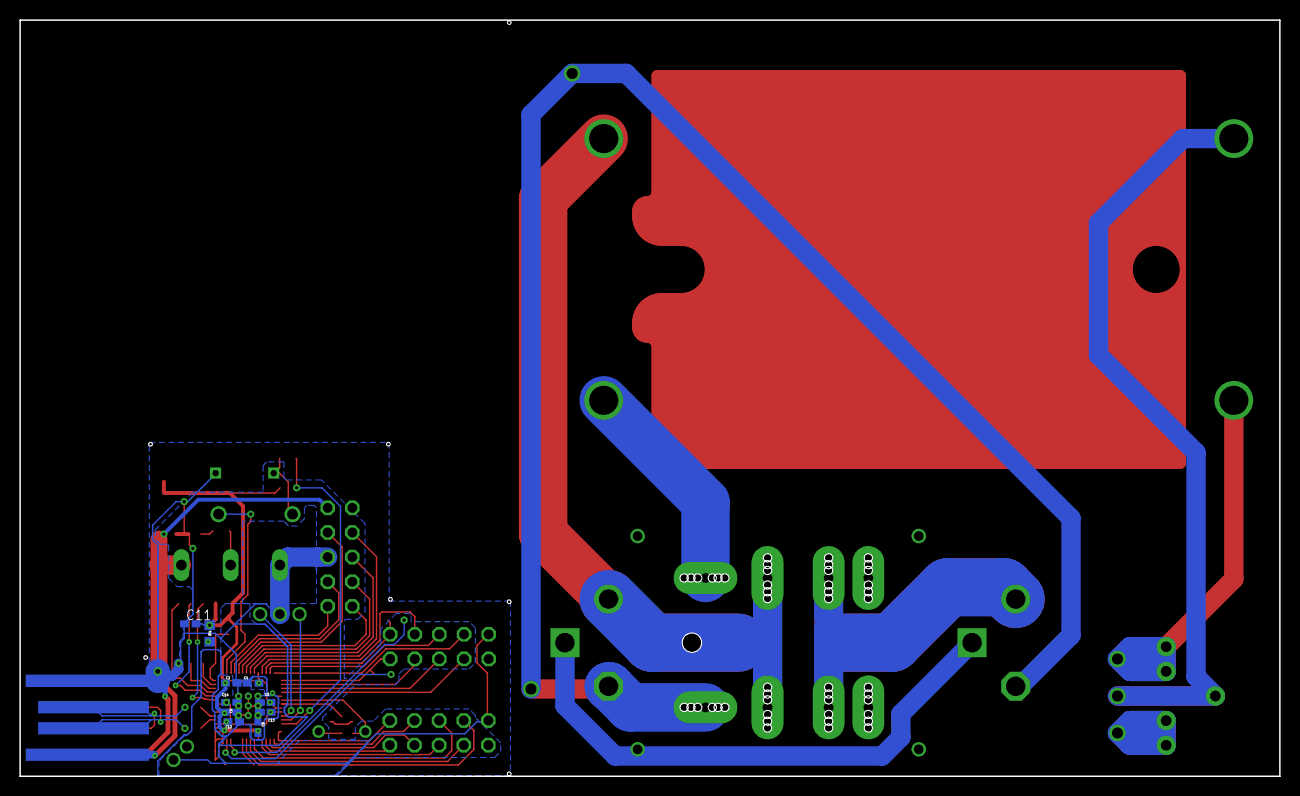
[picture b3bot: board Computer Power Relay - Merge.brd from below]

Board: 2 copper layers, 129.9 x 78.0 mm, 43 parts (10 on the bottom side), 55 nets.

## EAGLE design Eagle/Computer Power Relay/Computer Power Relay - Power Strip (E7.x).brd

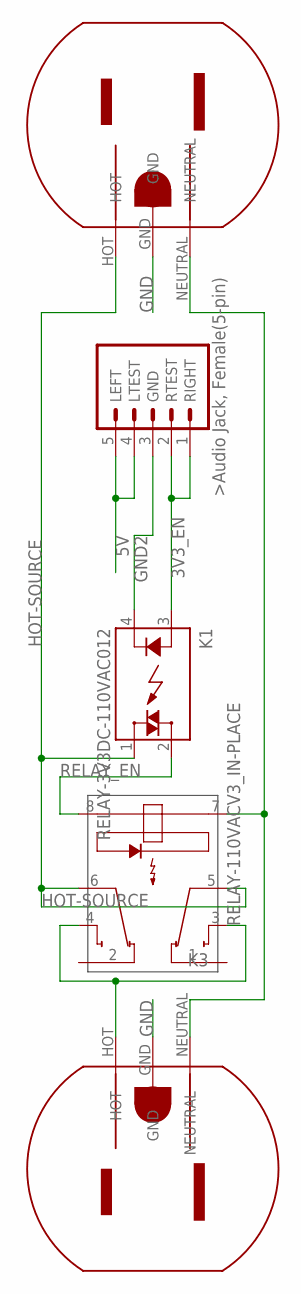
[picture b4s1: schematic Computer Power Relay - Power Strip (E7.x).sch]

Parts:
K1: RELAY-3V3DC-110VAC012; RELAY-3V3-110V
K3: RELAY-110VACV3_IN-PLACE; RELAY-110VAC-V3
U$1: AUDIO_JACK_FEMALE_5-PIN
U$2, U$3: MAINS-POWER-OUTLET3-PIN; 3-PIN-POWER

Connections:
3V3_EN: K1.3, U$1.1 (RIGHT), U$1.2 (RTEST)
5V: U$1.4 (LTEST), U$1.5 (LEFT)
GND: U$2.GND, U$3.GND
GND2: K1.4, U$1.3 (GND)
HOT-SOURCE: K1.1, K3.5, K3.6, U$3.HOT
unnamed: K3.3, K3.4, U$2.HOT
unnamed: K3.7, U$2.NEUTRAL, U$3.NEUTRAL
RELAY_EN: K1.2, K3.8

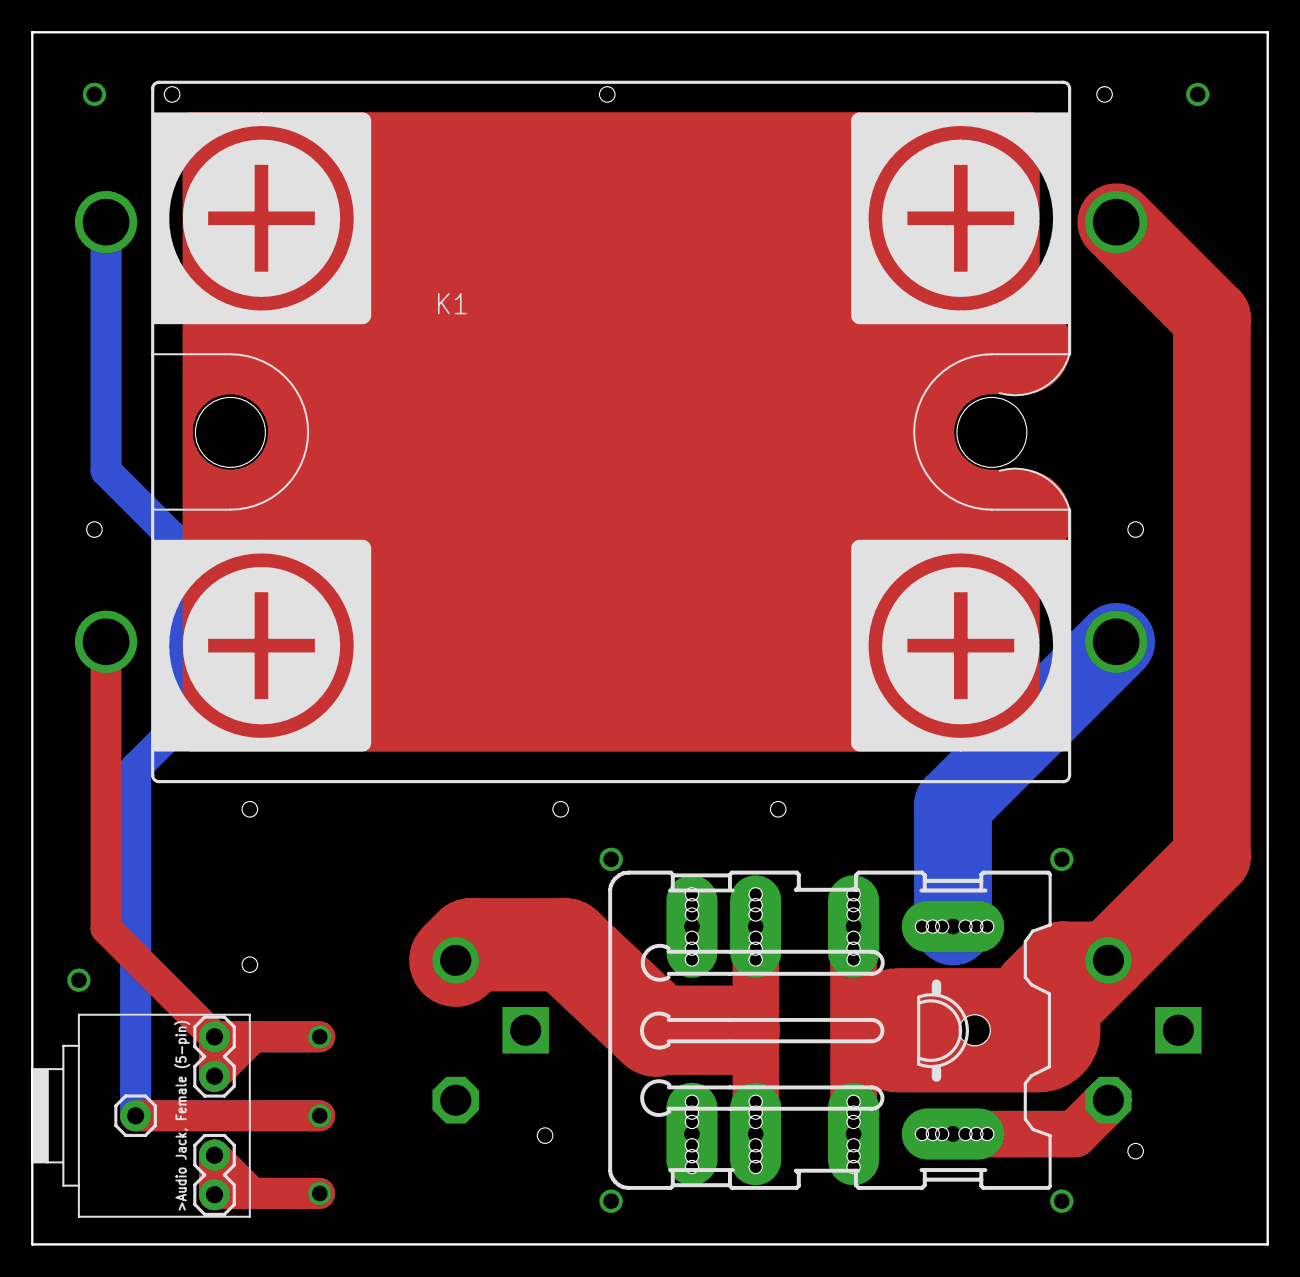
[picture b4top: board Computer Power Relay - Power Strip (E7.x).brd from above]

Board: 2 copper layers, 79.5 x 78.0 mm, 5 parts (0 on the bottom side), 8 nets.

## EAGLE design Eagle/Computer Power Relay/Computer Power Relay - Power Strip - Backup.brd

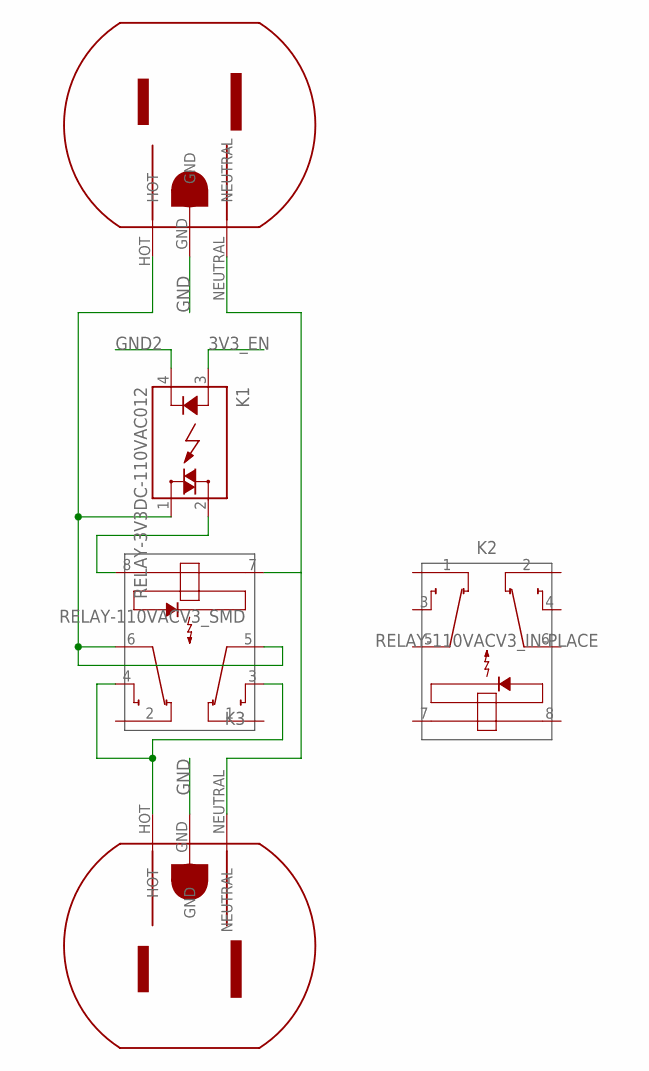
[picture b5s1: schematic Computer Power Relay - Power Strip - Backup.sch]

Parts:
K1: RELAY-3V3DC-110VAC012; RELAY-3V3-110V
K2: RELAY-110VACV3_IN-PLACE; RELAY-110VAC-V3
K3: RELAY-110VACV3_SMD; RELAY-110VAC-V3-SMD
U$1, U$2: MAINS-POWER-OUTLET3-PIN; 3-PIN-POWER

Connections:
3V3_EN: K1.3
GND: U$1.GND, U$2.GND
GND2: K1.4
unnamed: K3.3, K3.4, U$1.HOT
unnamed: K1.1, K3.5, K3.6, U$2.HOT
unnamed: K3.7, U$1.NEUTRAL, U$2.NEUTRAL
unnamed: K1.2, K3.8

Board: 2 copper layers, 5 parts (0 on the bottom side), 5 nets, no tracks yet.

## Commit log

2022-05-24 Switch and LED placement almost complete
    Key-switches, and rotary encoders are all in place. RGB LEDs are 80% in place. Rotary encoder LEDs are are not yet figured out.
2022-07-11 Bringing things up to date
2022-07-26 70% complete
2022-07-31 Power Relay 80%
2022-08-02 Split controller from power splitter
2022-08-09 Beginning Merge of Boards (Relay)
    I'm beginning to merge the Controller and Power Strip boards into one so that I can print it for cheaper.
2022-08-13 (CPR) 90% done, almost ready to send to fab
    Power Strip board is 100% complete.
    Controller board is 95% complete, all that's left is to figure out a method to restart into Boot Select with a single button press, and double-check that it works before sending it off to print.
    Remaining space of board is being filled out, and is nearly finished.
    I'm considering adding plated holes for spacer holes into the Power Strip board. We'll see.
2022-08-14 CPR Controller 98% complete
    Last thing to check is if the pins are arranged how I want them, and if I want to short stuff to ground instead of to GPIO.
2022-08-16 CPR 100% Complete
    Damn shipping's expensive. Better work on the other projects so I can subsidize this.
2022-08-25 Edited libraries & added USBs
    I edited library symbols to be more clear in the schematic about what they actually are. They should be much easier to understand than plain rectangles.
    I began adding USB ports, USB hub, and some RP2040s.
    When I left off, I was trying to redraw the symbol for a 2:2 mux for swapping between USB signals.
2022-08-26 Small update
2022-09-09 Begun Neopixel testing

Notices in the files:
parts and their libraries:
COPYRIGHT: Copyright (C) 2022 Ultra Librarian. All rights reserved.
SparkFun-Switches: Licensing: Creative Commons ShareAlike 4.0 International - https://creativecommons.org/licenses/by-sa/4.0
